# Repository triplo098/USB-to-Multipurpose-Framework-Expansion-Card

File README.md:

# USB-to-Multipurpose-Framework-Expansion-Card
This repository contains schematic, pcb design, production files and 3D case for custom made FT232H (USB to Multipurpose
UART/FIFO IC) Framework Expansion card.

## Features
- FTDI FT232H IC
- 2 x JST SH 6 pin connectors
- Fits the Framework Expansion Card (custom case in `3D_models`)

## Pinout

According to the [schematic](schematic_v1.0.pdf) card has two 6-pin connectors, **U3** and **U4**. Pin 1 is the GND pin at the left end of each connector in the PCB view.

### U3

| Pin | Signal | FT232H pin | Notes |
|-----|--------|------------|-------|
| 1 | GND | | Ground |
| 2 | +3.3V | | Supply output |
| 3 | SDA/MOSI | ADBUS1 (D1) | I²C SDA / SPI MOSI |
| 4 | SCL/SCK | ADBUS0 (D0) | I²C SCL / SPI SCK |
| 5 | SDA/MISO | ADBUS2 (D2) | I²C SDA / SPI MISO |
| 6 | CS | ADBUS3 (D3) | SPI chip select |

### U4

| Pin | Signal | FT232H pin | Notes |
|-----|--------|------------|-------|
| 1 | GND | | Ground |
| 2 | +5V | | Supply output |
| 3 | D7 | ADBUS7 | GPIO |
| 4 | C0 | ACBUS0 | GPIO |
| 5 | C8 | ACBUS8 | GPIO |
| 6 | C9 | ACBUS9 | GPIO |

## Repository structure

```text
.
├── usb_to_multipurpose/       # KiCad project (the actual board design)
├── 3D_models/                 # Enclosure and card models
├── images/                    # Renders used in this README
└── schematic_v1.0.pdf         # Exported schematic
```

### Third-party content and resources
- [Framework's Expansion Card repository](https://github.com/FrameworkComputer/ExpansionCards) (`Mechanical`): the mechanical of the card form factor. Files are located in `3D_models/ExpansionCard.*`:
- [FTDI FT232H Single Channel HiSpeed USB to Multipurpose
UART/FIFO IC datasheet](https://ftdichip.com/wp-content/uploads/2020/07/DS_FT232H.pdf): main resource for preparing the schematic and final PCB.
- [Adafruit FT232H Breakout](https://learn.adafruit.com/adafruit-ft232h-breakout/downloads): Adafruit documentation of the board that uses FT232H IC. It was used as a double check for schematic design.

## License

- Hardware design (KiCad project, schematic, production files): [CERN-OHL-P-2.0](LICENSE)
- 3D models, renders and documentation: [CC BY 4.0](LICENSE-docs)
- Framework Expansion Card mechanical files (`3D_models/ExpansionCard.*`): © 2021 Framework Computer Inc, [CC BY 4.0](https://creativecommons.org/licenses/by/4.0/). Source: [Framework repository](https://github.com/FrameworkComputer/ExpansionCards). Modified for this project's case.

## Credits
Great thanks ♥️ to [Flipp4](https://github.com/Flipp4) who did a great review of the board before version 0.

### PCB Renders

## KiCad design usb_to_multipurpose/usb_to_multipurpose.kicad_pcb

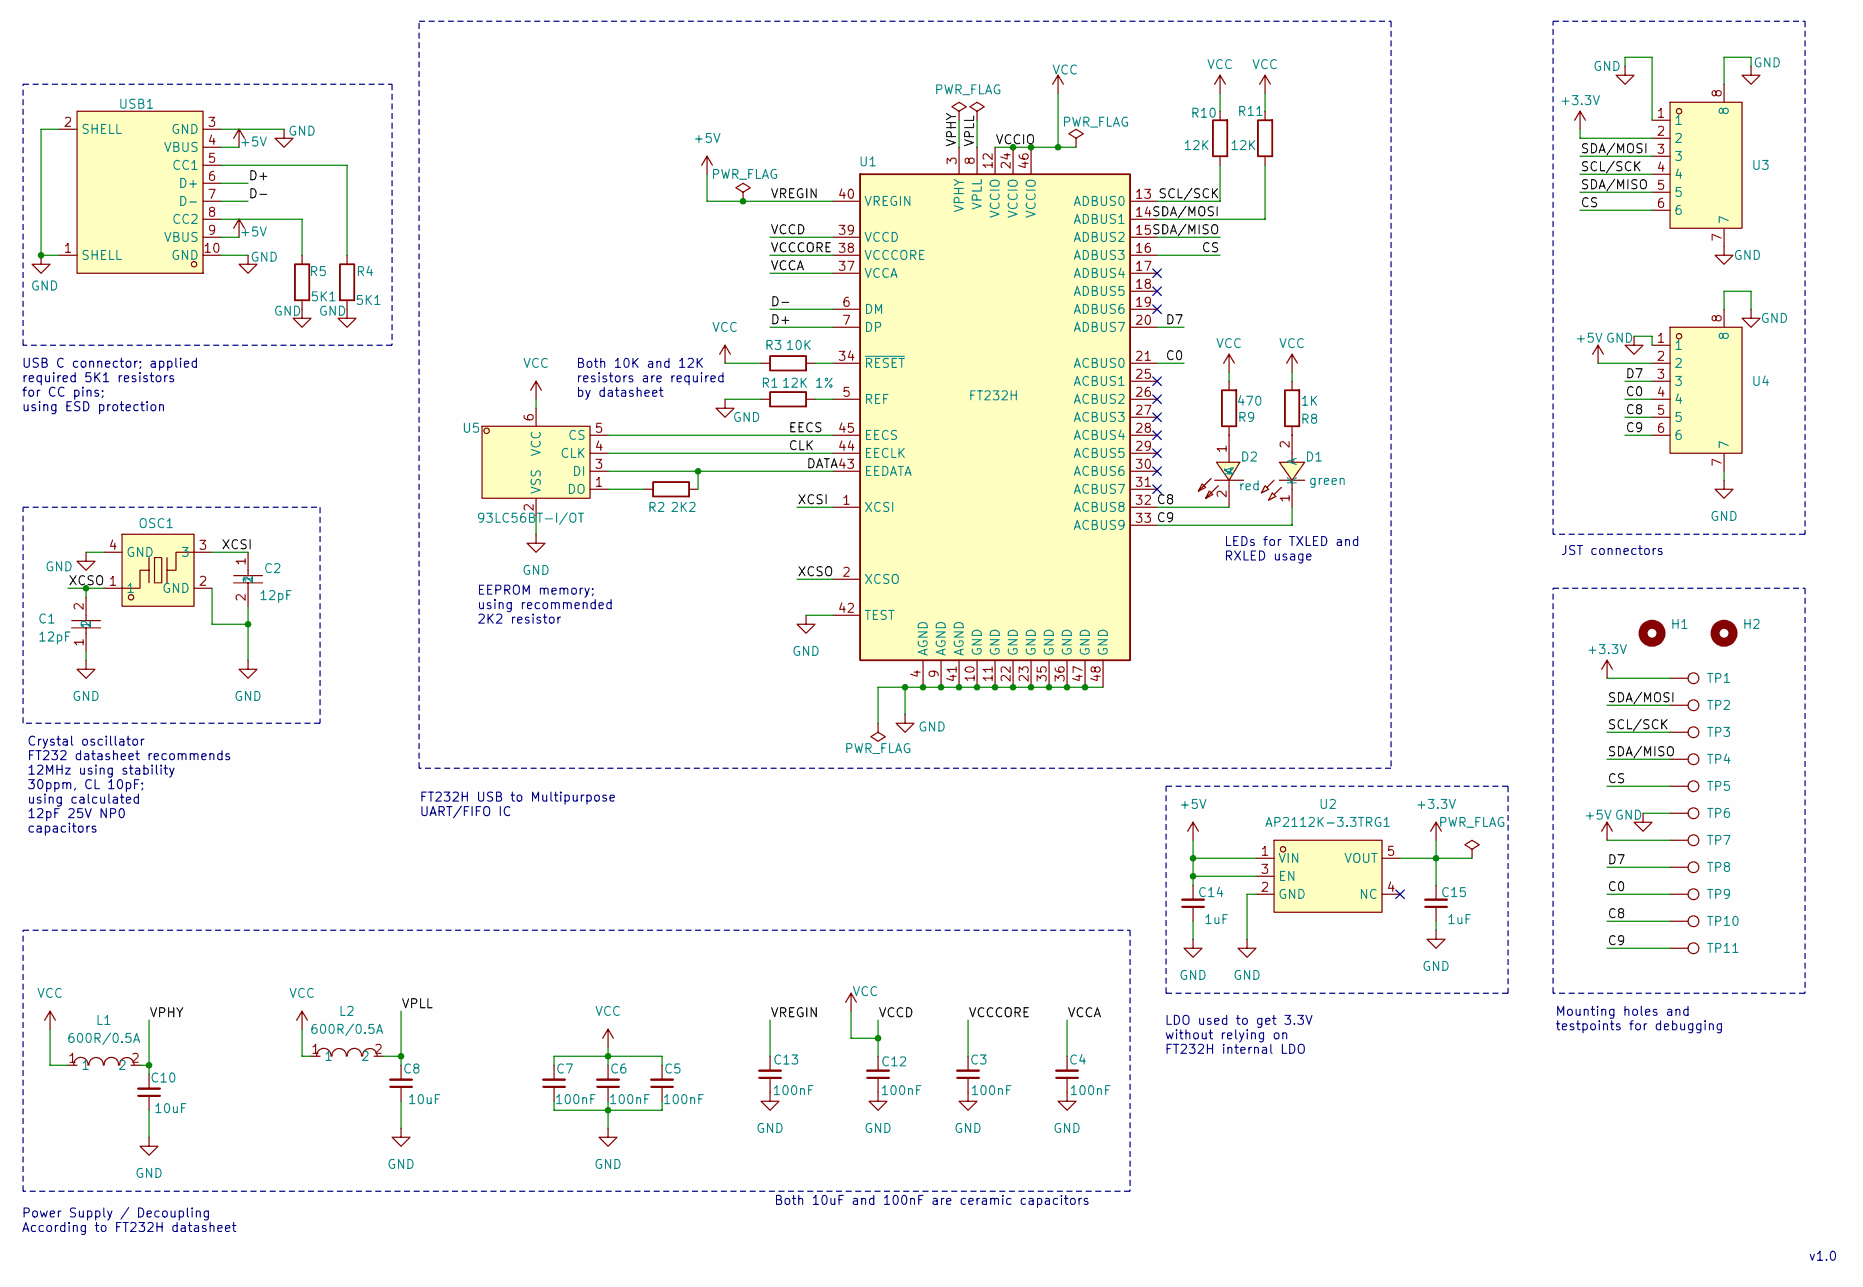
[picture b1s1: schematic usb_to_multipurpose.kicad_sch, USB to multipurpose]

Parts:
C1, C2: 12pF; C0402; MPN CC0402JRNPO9BN120; LCSC Part C106201
C3, C4, C5, C6, C7, C12, C13: 100nF; C0402
C8, C10: 10uF; C0603
C14, C15: 1uF; C0402
D1: green; LED0603-RD; MPN GL0603UG01; LCSC Part C51933293
D2: red; LED-SMD_L1.6-W0.8-R-RD; MPN KT-0603R; LCSC Part C2286
H1, H2: MountingHole; MountingHole_2.2mm_M2
L1, L2: 600R/0.5A; L0603; MPN BLM18EG601SN1D; LCSC Part C20345
OSC1: TX322512M4DBDE2T; OSC-SMD_4P-L3.2-W2.5-BL; MPN TX322512M4DBDE2T; LCSC Part C5310728
R1: 12K 1%; R0603
R2: 2K2; R0402
R3: 10K; R0402
R4, R5: 5K1; R0402
R8: 1K; R0603
R9: 470; R0603
R10, R11: 12K; R0603
TP1, TP2, TP3, TP4, TP5, TP6, TP7, TP8, TP9, TP10, TP11: TestPoint; TestPoint_Pad_1.0x1.0mm
U1: FT232H; LQFP-48_L7.0-W7.0-P0.50-LS9.0-TL
U2: AP2112K-3.3TRG1; SOT-23-5_L2.9-W1.6-P0.95-LS2.7-BR; MPN AP2112K-3.3TRG1(MS); LCSC Part C22365427
U3, U4: JST connector; CONN-SMD_SM06B-SRSS-TB-LF-SN; MPN SM06B-SRSS-TB(LF)(SN); LCSC Part C160405
U5: 93LC56BT-I/OT; SOT-23-6_L2.9-W1.6-P0.95-LS2.8-BR; MPN 93LC56BT-I/OT; LCSC Part C190271
USB1: HYCW675-USBC12-105B; USB-C-SMD_HYCW675-USBC12-105B; MPN HYCW675-USBC12-105B; LCSC Part C53436585

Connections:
+3.3V: C15.2, TP1.1 (1_1), U2.5 (VOUT), U3.2
+5V: C13.2, C14.2, TP7.1 (1_1), U1.40 (VREGIN), U2.1 (VIN), U2.3 (EN), U4.2, USB1.4 (VBUS), USB1.9 (VBUS)
/C0: TP9.1 (1_1), U1.21 (ACBUS0), U4.4
/C8: D2.2 (K), TP10.1 (1_1), U1.32 (ACBUS8), U4.5
/C9: D1.1 (K), TP11.1 (1_1), U1.33 (ACBUS9), U4.6
/CLK: U1.44 (EECLK), U5.4 (CLK)
/CS: TP5.1 (1_1), U1.16 (ADBUS3), U3.6
/D7: TP8.1 (1_1), U1.20 (ADBUS7), U4.3
/D+: U1.7 (DP), USB1.6 (D+)
/D-: U1.6 (DM), USB1.7 (D-)
/DATA: R2.2, U1.43 (EEDATA), U5.3 (DI)
/EECS: U1.45 (EECS), U5.5 (CS)
/SCL/SCK: R10.1, TP3.1 (1_1), U1.13 (ADBUS0), U3.4
/SDA/MISO: TP4.1 (1_1), U1.15 (ADBUS2), U3.5
/SDA/MOSI: R11.1, TP2.1 (1_1), U1.14 (ADBUS1), U3.3
/VCCA: C4.2, U1.37 (VCCA)
/VCCCORE: C3.2, U1.38 (VCCCORE)
/VPHY: C10.2, L1.2, U1.3 (VPHY)
/VPLL: C8.2, L2.2, U1.8 (VPLL)
/XCSI: C2.1, OSC1.3, U1.1 (XCSI)
/XCSO: C1.2, OSC1.1, U1.2 (XCSO)
GND: C1.1, C2.2, C3.1, C4.1, C5.1, C6.1, C7.1, C8.1, C10.1, C12.1, C13.1, C14.1, C15.1, OSC1.2 (GND), OSC1.4 (GND), R1.1, R4.2, R5.2, TP6.1 (1_1), U1.4 (AGND), U1.9 (AGND), U1.10 (GND), U1.11 (GND), U1.22 (GND), U1.23 (GND), U1.35 (GND), U1.36 (GND), U1.41 (AGND), U1.42 (TEST), U1.47 (GND), U1.48 (GND), U2.2 (GND), U3.1, U3.7, U3.8, U4.1, U4.7, U4.8, U5.2 (VSS), USB1.1 (SHELL), USB1.2 (SHELL), USB1.3 (GND), USB1.10 (GND)
unnamed: D1.2 (A), R8.1
unnamed: D2.1 (A), R9.1
unnamed: R1.2, U1.5 (REF)
unnamed: R3.2, U1.34 (~RESET)
unnamed: R2.1, U5.1 (DO)
unnamed: R4.1, USB1.5 (CC1)
unnamed: R5.1, USB1.8 (CC2)
VCC: C5.2, C6.2, C7.2, C12.2, L1.1, L2.1, R3.1, R8.2, R9.2, R10.2, R11.2, U1.12 (VCCIO), U1.24 (VCCIO), U1.39 (VCCD), U1.46 (VCCIO), U5.6 (VCC)

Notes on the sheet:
LEDs for TXLED and RXLED usage
v1.0
JST connectors
Mounting holes and testpoints for debugging
FT232H USB to Multipurpose UART/FIFO IC
Power Supply / Decoupling According to FT232H datasheet
USB C connector; applied required 5K1 resistors for CC pins; using ESD protection
Crystal oscillator FT232 datasheet recommends 12MHz using stability 30ppm, CL 10pF; using calculated 12pF 25V NP0 capacitors
Both 10K and 12K resistors are required by datasheet
EEPROM memory; using recommended 2K2 resistor
LDO used to get 3.3V without relying on FT232H internal LDO
Both 10uF and 100nF are ceramic capacitors

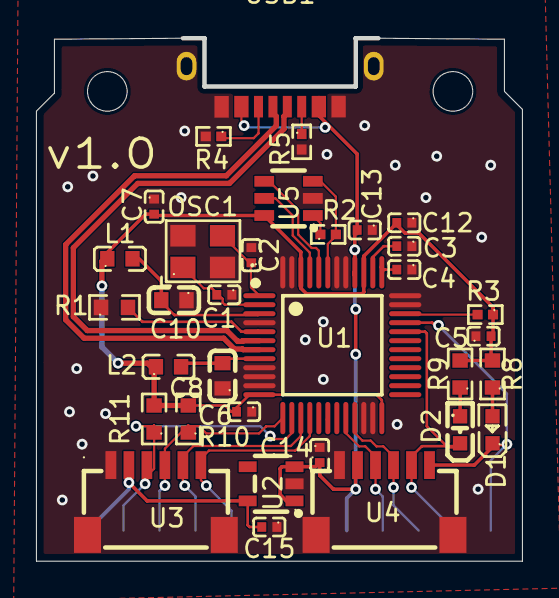
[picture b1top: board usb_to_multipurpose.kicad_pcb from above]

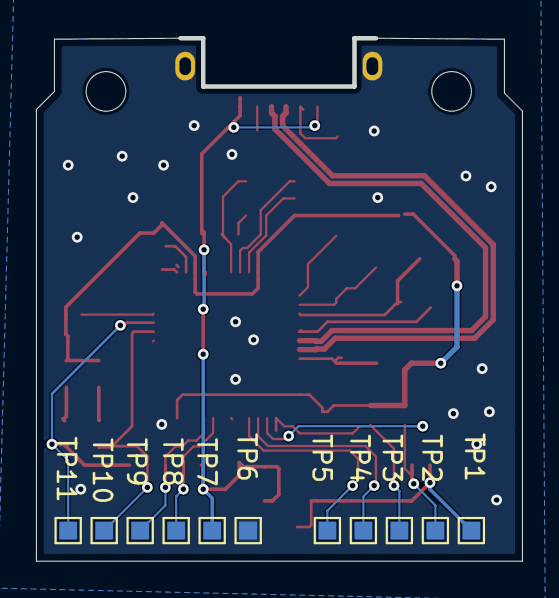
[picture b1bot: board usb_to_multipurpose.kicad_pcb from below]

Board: 2 copper layers, 27.0 x 29.1 mm, 46 parts (11 on the bottom side), 30 nets.
